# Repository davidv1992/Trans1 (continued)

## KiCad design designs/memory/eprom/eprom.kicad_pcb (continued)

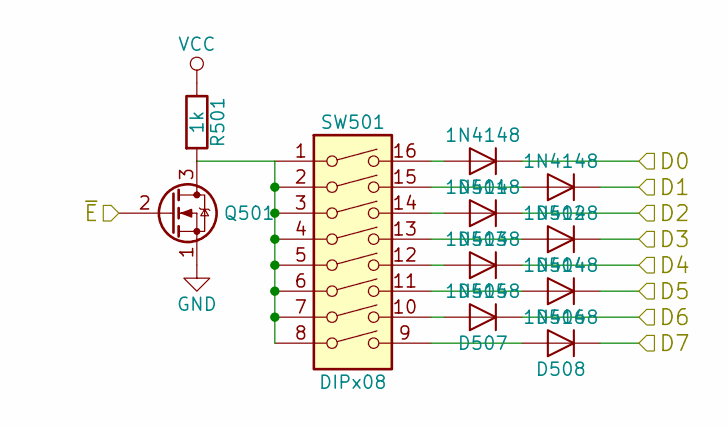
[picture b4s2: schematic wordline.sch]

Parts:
D201, D202, D203, D204, D205, D206, D207, D208: 1N4148; D_default
Q201: 2N7000; TO-92-FET
R201: 1k; R_small
SW201: DIPx08; DIPx8

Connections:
/wordline_0/D0: D201.1 (K); also elsewhere on the board
/wordline_0/D1: D202.1 (K); also elsewhere on the board
/wordline_0/D2: D203.1 (K); also elsewhere on the board
/wordline_0/D3: D204.1 (K); also elsewhere on the board
/wordline_0/~E: Q201.2 (G); also elsewhere on the board
/wordline_4/D0: D208.1 (K); also elsewhere on the board
/wordline_4/D1: D207.1 (K); also elsewhere on the board
/wordline_4/D2: D206.1 (K); also elsewhere on the board
/wordline_4/D3: D205.1 (K); also elsewhere on the board
GND: Q201.1 (S); also elsewhere on the board
unnamed: D201.2 (A), SW201.16
unnamed: D202.2 (A), SW201.15
unnamed: D203.2 (A), SW201.14
unnamed: D204.2 (A), SW201.13
unnamed: D205.2 (A), SW201.12
unnamed: D206.2 (A), SW201.11
unnamed: D207.2 (A), SW201.10
unnamed: D208.2 (A), SW201.9
unnamed: Q201.3 (D), R201.2, SW201.1, SW201.2, SW201.3, SW201.4, SW201.5, SW201.6, SW201.7, SW201.8
VCC: R201.1; also elsewhere on the board

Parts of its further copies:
D301, D302, D303, D304, D305, D306, D307, D308, D401, D402, D403, D404, D405, D406, D407, D408, D501, D502, D503, D504, D505, D506, D507, D508, D601, D602, D603, D604, D605, D606, D607, D608, D701, D702, D703, D704, D705, D706, D707, D708, D801, D802, D803, D804, D805, D806, D807, D808, D901, D902, D903, D904, D905, D906, D907, D908: 1N4148; D_default
Q301, Q401, Q501, Q601, Q701, Q801, Q901: 2N7000; TO-92-FET
R301, R401, R501, R601, R701, R801, R901: 1k; R_small
SW301, SW401, SW501, SW601, SW701, SW801, SW901: DIPx08; DIPx8

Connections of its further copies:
/wordline_0/D0: D301.1 (K), D401.1 (K), D501.1 (K), D608.1 (K), D708.1 (K), D808.1 (K), D908.1 (K); also elsewhere on the board
/wordline_0/D1: D302.1 (K), D402.1 (K), D502.1 (K), D607.1 (K), D707.1 (K), D807.1 (K), D907.1 (K); also elsewhere on the board
/wordline_0/D2: D303.1 (K), D403.1 (K), D503.1 (K), D606.1 (K), D706.1 (K), D806.1 (K), D906.1 (K); also elsewhere on the board
/wordline_0/D3: D304.1 (K), D404.1 (K), D504.1 (K), D605.1 (K), D705.1 (K), D805.1 (K), D905.1 (K); also elsewhere on the board
/wordline_1/~E: Q301.2 (G); also elsewhere on the board
/wordline_2/~E: Q401.2 (G); also elsewhere on the board
/wordline_3/~E: Q501.2 (G); also elsewhere on the board
/wordline_4/D0: D308.1 (K), D408.1 (K), D508.1 (K), D601.1 (K), D701.1 (K), D801.1 (K), D901.1 (K); also elsewhere on the board
/wordline_4/D1: D307.1 (K), D407.1 (K), D507.1 (K), D602.1 (K), D702.1 (K), D802.1 (K), D902.1 (K); also elsewhere on the board
/wordline_4/D2: D306.1 (K), D406.1 (K), D506.1 (K), D603.1 (K), D703.1 (K), D803.1 (K), D903.1 (K); also elsewhere on the board
/wordline_4/D3: D305.1 (K), D405.1 (K), D505.1 (K), D604.1 (K), D704.1 (K), D804.1 (K), D904.1 (K); also elsewhere on the board
/wordline_4/~E: Q601.2 (G); also elsewhere on the board
/wordline_5/~E: Q701.2 (G); also elsewhere on the board
/wordline_6/~E: Q801.2 (G); also elsewhere on the board
/wordline_7/~E: Q901.2 (G); also elsewhere on the board
GND: Q301.1 (S), Q401.1 (S), Q501.1 (S), Q601.1 (S), Q701.1 (S), Q801.1 (S), Q901.1 (S); also elsewhere on the board
unnamed: D301.2 (A), SW301.16
unnamed: D302.2 (A), SW301.15
unnamed: D303.2 (A), SW301.14
unnamed: D304.2 (A), SW301.13
unnamed: D305.2 (A), SW301.12
unnamed: D306.2 (A), SW301.11
unnamed: D307.2 (A), SW301.10
unnamed: D308.2 (A), SW301.9
unnamed: D401.2 (A), SW401.16
unnamed: D402.2 (A), SW401.15
unnamed: D403.2 (A), SW401.14
unnamed: D404.2 (A), SW401.13
unnamed: D405.2 (A), SW401.12
unnamed: D406.2 (A), SW401.11
unnamed: D407.2 (A), SW401.10
unnamed: D408.2 (A), SW401.9
unnamed: D501.2 (A), SW501.16
unnamed: D502.2 (A), SW501.15
unnamed: D503.2 (A), SW501.14
unnamed: D504.2 (A), SW501.13
unnamed: D505.2 (A), SW501.12
unnamed: D506.2 (A), SW501.11
unnamed: D507.2 (A), SW501.10
unnamed: D508.2 (A), SW501.9
unnamed: D601.2 (A), SW601.16
unnamed: D602.2 (A), SW601.15
unnamed: D603.2 (A), SW601.14
unnamed: D604.2 (A), SW601.13
unnamed: D605.2 (A), SW601.12
unnamed: D606.2 (A), SW601.11
unnamed: D607.2 (A), SW601.10
unnamed: D608.2 (A), SW601.9
unnamed: D701.2 (A), SW701.16
unnamed: D702.2 (A), SW701.15
unnamed: D703.2 (A), SW701.14
unnamed: D704.2 (A), SW701.13
unnamed: D705.2 (A), SW701.12
unnamed: D706.2 (A), SW701.11
unnamed: D707.2 (A), SW701.10
unnamed: D708.2 (A), SW701.9
unnamed: D801.2 (A), SW801.16
unnamed: D802.2 (A), SW801.15
unnamed: D803.2 (A), SW801.14
unnamed: D804.2 (A), SW801.13
unnamed: D805.2 (A), SW801.12
unnamed: D806.2 (A), SW801.11
unnamed: D807.2 (A), SW801.10
unnamed: D808.2 (A), SW801.9
unnamed: D901.2 (A), SW901.16
unnamed: D902.2 (A), SW901.15
unnamed: D903.2 (A), SW901.14
unnamed: D904.2 (A), SW901.13
unnamed: D905.2 (A), SW901.12
unnamed: D906.2 (A), SW901.11
unnamed: D907.2 (A), SW901.10
unnamed: D908.2 (A), SW901.9
unnamed: Q301.3 (D), R301.2, SW301.1, SW301.2, SW301.3, SW301.4, SW301.5, SW301.6, SW301.7, SW301.8
unnamed: Q401.3 (D), R401.2, SW401.1, SW401.2, SW401.3, SW401.4, SW401.5, SW401.6, SW401.7, SW401.8
unnamed: Q501.3 (D), R501.2, SW501.1, SW501.2, SW501.3, SW501.4, SW501.5, SW501.6, SW501.7, SW501.8
unnamed: Q601.3 (D), R601.2, SW601.1, SW601.2, SW601.3, SW601.4, SW601.5, SW601.6, SW601.7, SW601.8
unnamed: Q701.3 (D), R701.2, SW701.1, SW701.2, SW701.3, SW701.4, SW701.5, SW701.6, SW701.7, SW701.8
unnamed: Q801.3 (D), R801.2, SW801.1, SW801.2, SW801.3, SW801.4, SW801.5, SW801.6, SW801.7, SW801.8
unnamed: Q901.3 (D), R901.2, SW901.1, SW901.2, SW901.3, SW901.4, SW901.5, SW901.6, SW901.7, SW901.8
VCC: R301.1, R401.1, R501.1, R601.1, R701.1, R801.1, R901.1; also elsewhere on the board

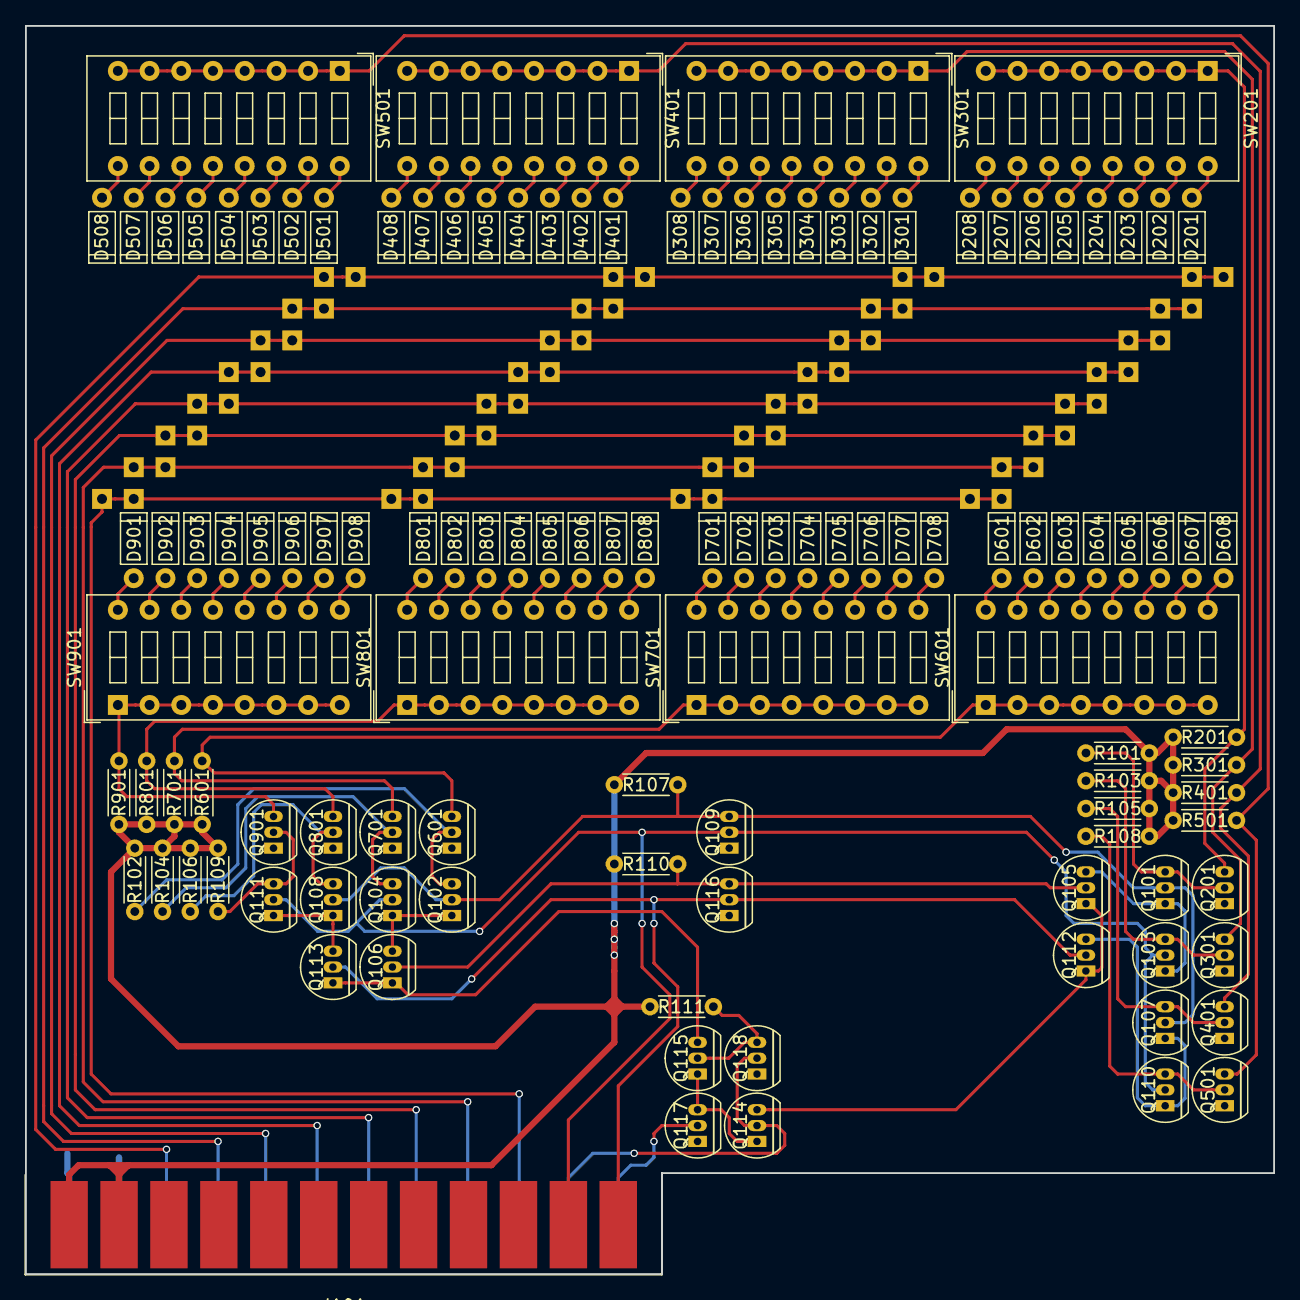
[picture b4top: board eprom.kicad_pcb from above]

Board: 2 copper layers, 100.0 x 100.0 mm, 118 parts (0 on the bottom side), 104 nets.

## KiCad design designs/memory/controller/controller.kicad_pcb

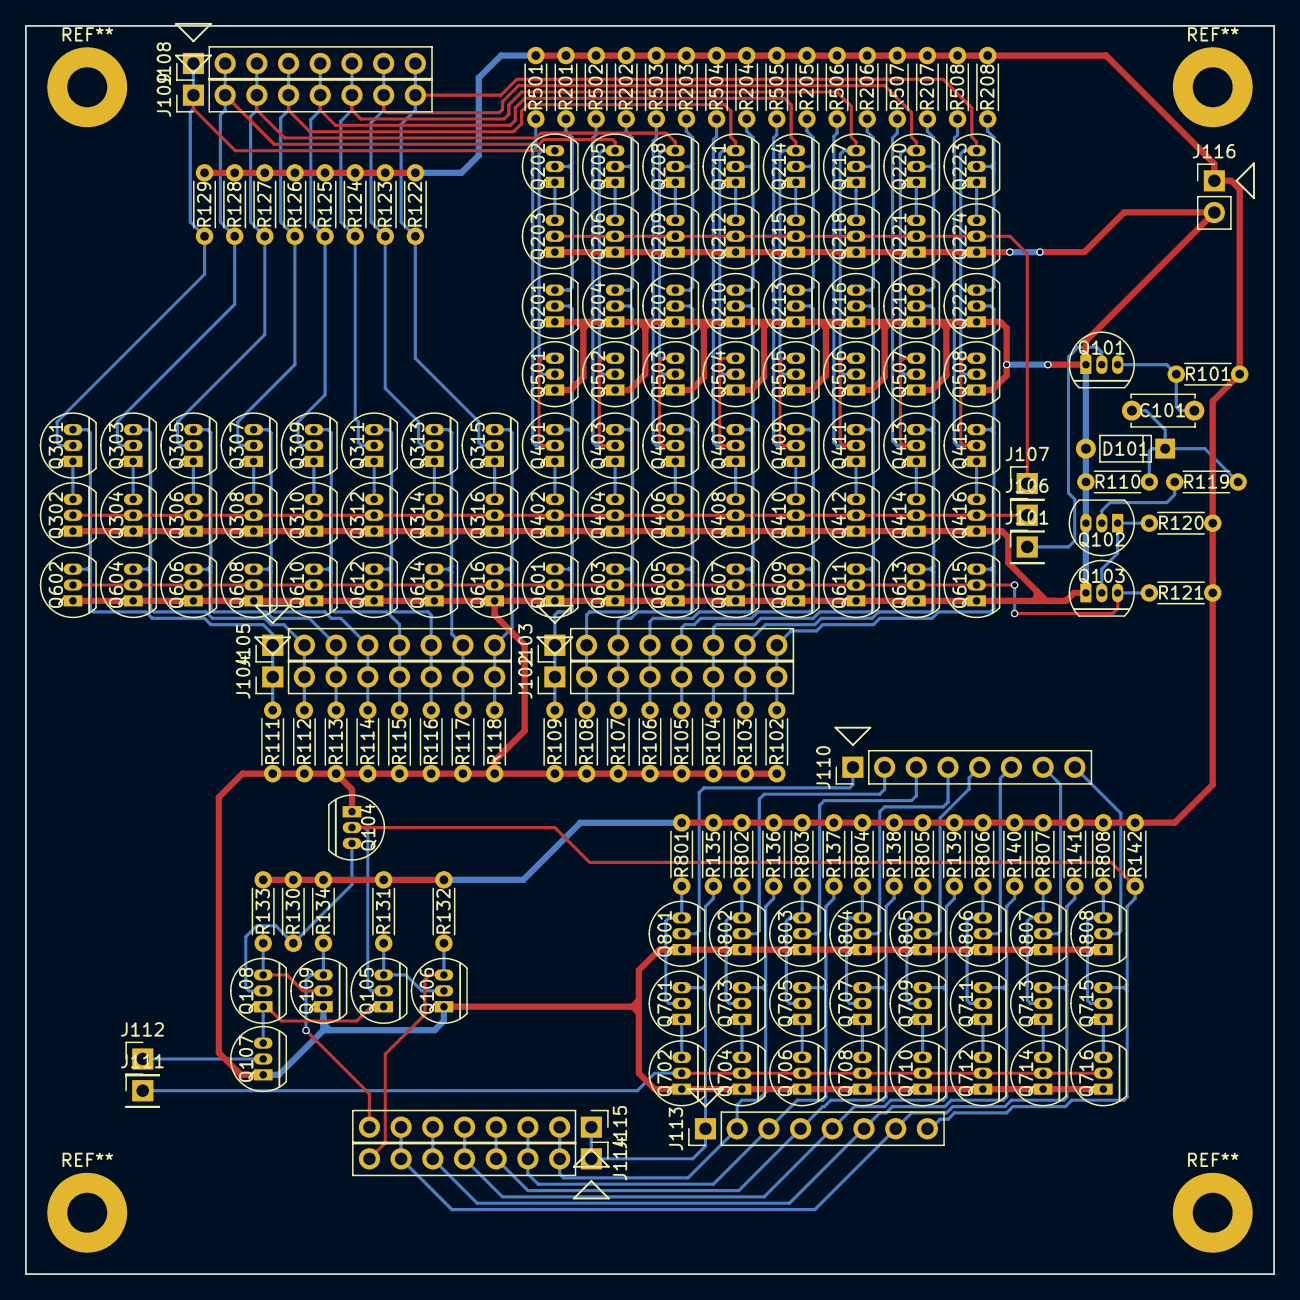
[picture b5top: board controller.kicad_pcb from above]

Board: 2 copper layers, 100.0 x 100.0 mm, 197 parts (0 on the bottom side), 114 nets.

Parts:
C101: 100pf; C_default
D101: 1N4148; D_default
J101, J106, J107, J111, J112: Conn_01x01; PH_1x1
J102, J103, J104, J105, J108, J109, J110, J113, J114, J115: Conn_01x08; PH_1x8
J116: Conn_01x02_Power; PH_1x2
Q101, Q103, Q104, Q105, Q106, Q107, Q108, Q109, Q201, Q202, Q203, Q204, Q205, Q206, Q207, Q208, Q209, Q210, Q211, Q212, Q213, Q214, Q215, Q216, Q217, Q218, Q219, Q220, Q221, Q222, Q223, Q224, Q301, Q302, Q303, Q304, Q305, Q306, Q307, Q308, Q309, Q310, Q311, Q312, Q313, Q314, Q315, Q316, Q401, Q402, Q403, Q404, Q405, Q406, Q407, Q408, Q409, Q410, Q411, Q412, Q413, Q414, Q415, Q416, Q501, Q502, Q503, Q504, Q505, Q506, Q507, Q508, Q601, Q602, Q603, Q604, Q605, Q606, Q607, Q608, Q609, Q610, Q611, Q612, Q613, Q614, Q615, Q616, Q701, Q702, Q703, Q704, Q705, Q706, Q707, Q708, Q709, Q710, Q711, Q712, Q713, Q714, Q715, Q716, Q801, Q802, Q803, Q804, Q805, Q806, Q807, Q808: 2N7000; TO-92-FET
Q102: BC547; TO-92-BJT
R101, R110, R120, R121, R122, R123, R124, R125, R126, R127, R128, R129, R130, R131, R132, R133, R134, R135, R136, R137, R138, R139, R140, R141, R142, R501, R502, R503, R504, R505, R506, R507, R508, R801, R802, R803, R804, R805, R806, R807, R808: 1k; R_small
R102, R103, R104, R105, R106, R107, R108, R109, R111, R112, R113, R114, R115, R116, R117, R118: 100k; R_small
R119: 10k; R_small
R201, R202, R203, R204, R205, R206, R207, R208: R; R_small

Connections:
/Ten/A0: J113.1, J114.1, J115.1, Q701.3, R135.2
/Ten/A1: J113.2, J114.2, J115.2, Q703.3, R136.2
/Ten/A2: J113.3, J114.3, J115.3, Q705.3, R137.2
/Ten/A3: J113.4, J114.4, J115.4, Q707.3, R138.2
/Ten/A4: J113.5, J114.5, J115.5, Q709.3, R139.2
/Ten/A5: J113.6, J114.6, J115.6, Q711.3, R140.2
/Ten/A6: J113.7, J114.7, J115.7, Q713.3, R141.2
/Ten/A7: J113.8, Q104.2, Q105.2, Q715.3, R142.2
/Ten/En: J111.1, Q702.2, Q704.2, Q706.2, Q708.2, Q710.2, Q712.2, Q714.2, Q716.2
/Ten/T0: Q701.2, Q801.3, R801.2
/Ten/T1: Q703.2, Q802.3, R802.2
/Ten/T2: Q705.2, Q803.3, R803.2
/Ten/T3: Q707.2, Q804.3, R804.2
/Ten/T4: Q709.2, Q805.3, R805.2
/Ten/T5: Q711.2, Q806.3, R806.2
/Ten/T6: Q713.2, Q807.3, R807.2
/Ten/T7: Q715.2, Q808.3, R808.2
/clear/Clr: Q103.3, Q601.2, Q602.2, Q603.2, Q604.2, Q605.2, Q606.2, Q607.2, Q608.2, Q609.2, Q610.2, Q611.2, Q612.2, Q613.2, Q614.2, Q615.2, Q616.2, R121.2
/clear/D0: J102.1, J103.1, Q201.2, Q401.3, Q601.3, R109.2
/clear/D1: J102.2, J103.2, Q204.2, Q403.3, Q603.3, R108.2
/clear/D2: J102.3, J103.3, Q207.2, Q405.3, Q605.3, R107.2
/clear/D3: J102.4, J103.4, Q210.2, Q407.3, Q607.3, R106.2
/clear/D4: J102.5, J103.5, Q213.2, Q409.3, Q609.3, R105.2
/clear/D5: J102.6, J103.6, Q216.2, Q411.3, Q611.3, R104.2
/clear/D6: J102.7, J103.7, Q219.2, Q413.3, Q613.3, R103.2
/clear/D7: J102.8, J103.8, Q222.2, Q415.3, Q615.3, R102.2
/clear/D8: J104.1, J105.1, Q301.3, Q602.3, R111.1
/clear/D9: J104.2, J105.2, Q303.3, Q604.3, R112.1
/clear/D10: J104.3, J105.3, Q305.3, Q606.3, R113.1
/clear/D11: J104.4, J105.4, Q307.3, Q608.3, R114.1
/clear/D12: J104.5, J105.5, Q309.3, Q610.3, R115.1
/clear/D13: J104.6, J105.6, Q311.3, Q612.3, R116.1
/clear/D14: J104.7, J105.7, Q313.3, Q614.3, R117.1
/clear/D15: J104.8, J105.8, Q315.3, Q616.3, R118.1
/inv2/D0: J110.1, Q801.2
/inv2/D1: J110.2, Q802.2
/inv2/D2: J110.3, Q803.2
/inv2/D3: J110.4, Q804.2
/inv2/D4: J110.5, Q805.2
/inv2/D5: J110.6, Q806.2
/inv2/D6: J110.7, Q807.2
/inv2/D7: J110.8, Q808.2
/inv/D0: J108.1, J109.1, Q202.3, Q301.2, Q501.2, R129.2
/inv/D1: J108.2, J109.2, Q205.3, Q303.2, Q502.2, R128.2
/inv/D2: J108.3, J109.3, Q208.3, Q305.2, Q503.2, R127.2
/inv/D3: J108.4, J109.4, Q211.3, Q307.2, Q504.2, R126.2
/inv/D4: J108.5, J109.5, Q214.3, Q309.2, Q505.2, R125.2
/inv/D5: J108.6, J109.6, Q217.3, Q311.2, Q506.2, R124.2
/inv/D6: J108.7, J109.7, Q220.3, Q313.2, Q507.2, R123.2
/inv/D7: J108.8, J109.8, Q223.3, Q315.2, Q508.2, R122.2
/sense/En: J107.1, Q203.2, Q206.2, Q209.2, Q212.2, Q215.2, Q218.2, Q221.2, Q224.2
/writeNeg/En: J106.1, Q302.2, Q304.2, Q306.2, Q308.2, Q310.2, Q312.2, Q314.2, Q316.2, Q402.2, Q404.2, Q406.2, Q408.2, Q410.2, Q412.2, Q414.2, Q416.2
/writePos/D0: Q401.2, Q501.3, R501.2
/writePos/D1: Q403.2, Q502.3, R502.2
/writePos/D2: Q405.2, Q503.3, R503.2
/writePos/D3: Q407.2, Q504.3, R504.2
/writePos/D4: Q409.2, Q505.3, R505.2
/writePos/D5: Q411.2, Q506.3, R506.2
/writePos/D6: Q413.2, Q507.3, R507.2
/writePos/D7: Q415.2, Q508.3, R508.2
GND: D101.2, J116.2, Q101.1, Q102.3, Q103.1, Q104.1, Q106.1, Q107.1, Q109.1, Q201.1, Q203.1, Q204.1, Q206.1, Q207.1, Q209.1, Q210.1, Q212.1, Q213.1, Q215.1, Q216.1, Q218.1, Q219.1, Q221.1, Q222.1, Q224.1, Q302.1, Q304.1, Q306.1, Q308.1, Q310.1, Q312.1, Q314.1, Q316.1, Q402.1, Q404.1, Q406.1, Q408.1, Q410.1, Q412.1, Q414.1, Q416.1, Q501.1, Q502.1, Q503.1, Q504.1, Q505.1, Q506.1, Q507.1, Q508.1, Q601.1, Q602.1, Q603.1, Q604.1, Q605.1, Q606.1, Q607.1, Q608.1, Q609.1, Q610.1, Q611.1, Q612.1, Q613.1, Q614.1, Q615.1, Q616.1, Q702.1, Q704.1, Q706.1, Q708.1, Q710.1, Q712.1, Q714.1, Q716.1, Q801.1, Q802.1, Q803.1, Q804.1, Q805.1, Q806.1, Q807.1, Q808.1, R102.1, R103.1, R104.1, R105.1, R106.1, R107.1, R108.1, R109.1, R110.2, R111.2, R112.2, R113.2, R114.2, R115.2, R116.2, R117.2, R118.2
unnamed: C101.1, Q101.3, R101.2
unnamed: C101.2, D101.1, R110.1, R119.2
unnamed: J101.1, Q101.2
unnamed: J112.1, Q107.2
unnamed: J114.8, Q106.3, R132.2
unnamed: J115.8, Q109.3, R134.2
unnamed: Q102.1, Q103.2, R120.2
unnamed: Q102.2, R119.1
unnamed: Q104.3, Q108.2, R130.2
unnamed: Q105.1, Q107.3, Q108.1
unnamed: Q105.3, Q106.2, R131.2
unnamed: Q108.3, Q109.2, R133.2
unnamed: Q201.3, Q202.2, R201.2
unnamed: Q202.1, Q203.3
unnamed: Q204.3, Q205.2, R202.2
unnamed: Q205.1, Q206.3
unnamed: Q207.3, Q208.2, R203.2
unnamed: Q208.1, Q209.3
unnamed: Q210.3, Q211.2, R204.2
unnamed: Q211.1, Q212.3
unnamed: Q213.3, Q214.2, R205.2
unnamed: Q214.1, Q215.3
unnamed: Q216.3, Q217.2, R206.2
unnamed: Q217.1, Q218.3
unnamed: Q219.3, Q220.2, R207.2
unnamed: Q220.1, Q221.3
unnamed: Q222.3, Q223.2, R208.2
unnamed: Q223.1, Q224.3
unnamed: Q301.1, Q302.3
unnamed: Q303.1, Q304.3
unnamed: Q305.1, Q306.3
unnamed: Q307.1, Q308.3
unnamed: Q309.1, Q310.3
unnamed: Q311.1, Q312.3
unnamed: Q313.1, Q314.3
unnamed: Q315.1, Q316.3
unnamed: Q401.1, Q402.3
unnamed: Q403.1, Q404.3
unnamed: Q405.1, Q406.3
unnamed: Q407.1, Q408.3
unnamed: Q409.1, Q410.3
unnamed: Q411.1, Q412.3
unnamed: Q413.1, Q414.3
unnamed: Q415.1, Q416.3
unnamed: Q701.1, Q702.3
unnamed: Q703.1, Q704.3
unnamed: Q705.1, Q706.3
unnamed: Q707.1, Q708.3
unnamed: Q709.1, Q710.3
unnamed: Q711.1, Q712.3
unnamed: Q713.1, Q714.3
unnamed: Q715.1, Q716.3
VCC: J116.1, R101.1, R120.1, R121.1, R122.1, R123.1, R124.1, R125.1, R126.1, R127.1, R128.1, R129.1, R130.1, R131.1, R132.1, R133.1, R134.1, R135.1, R136.1, R137.1, R138.1, R139.1, R140.1, R141.1, R142.1, R201.1, R202.1, R203.1, R204.1, R205.1, R206.1, R207.1, R208.1, R501.1, R502.1, R503.1, R504.1, R505.1, R506.1, R507.1, R508.1, R801.1, R802.1, R803.1, R804.1, R805.1, R806.1, R807.1, R808.1

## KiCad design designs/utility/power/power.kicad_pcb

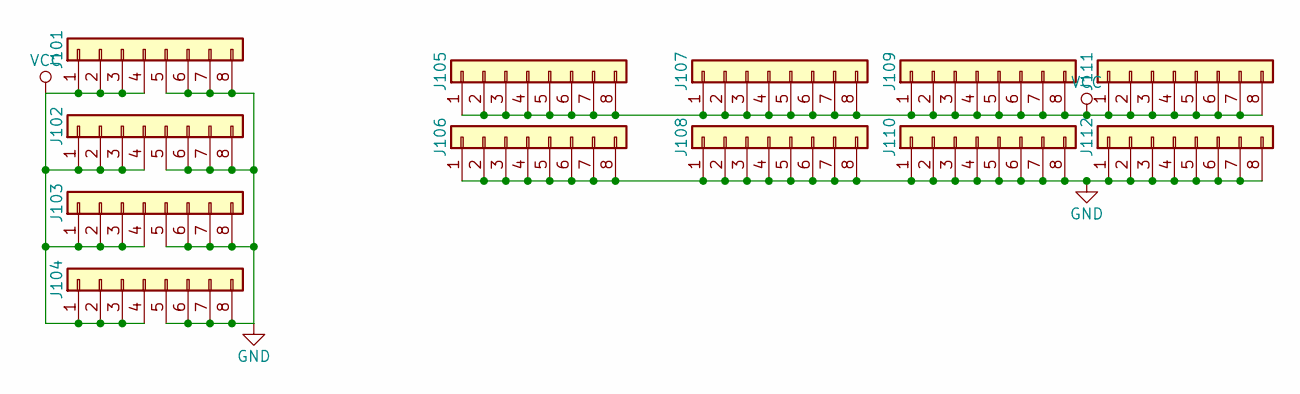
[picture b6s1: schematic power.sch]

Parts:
J101, J102, J103, J104, J105, J106, J107, J108, J109, J110, J111, J112: Conn_01x08; PH_1x8

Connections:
GND: J101.5, J101.6, J101.7, J101.8, J102.5, J102.6, J102.7, J102.8, J103.5, J103.6, J103.7, J103.8, J104.5, J104.6, J104.7, J104.8, J106.1, J106.2, J106.3, J106.4, J106.5, J106.6, J106.7, J106.8, J108.1, J108.2, J108.3, J108.4, J108.5, J108.6, J108.7, J108.8, J110.1, J110.2, J110.3, J110.4, J110.5, J110.6, J110.7, J110.8, J112.1, J112.2, J112.3, J112.4, J112.5, J112.6, J112.7, J112.8
VCC: J101.1, J101.2, J101.3, J101.4, J102.1, J102.2, J102.3, J102.4, J103.1, J103.2, J103.3, J103.4, J104.1, J104.2, J104.3, J104.4, J105.1, J105.2, J105.3, J105.4, J105.5, J105.6, J105.7, J105.8, J107.1, J107.2, J107.3, J107.4, J107.5, J107.6, J107.7, J107.8, J109.1, J109.2, J109.3, J109.4, J109.5, J109.6, J109.7, J109.8, J111.1, J111.2, J111.3, J111.4, J111.5, J111.6, J111.7, J111.8

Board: 2 copper layers, 12 parts (0 on the bottom side), 2 nets, no tracks yet.

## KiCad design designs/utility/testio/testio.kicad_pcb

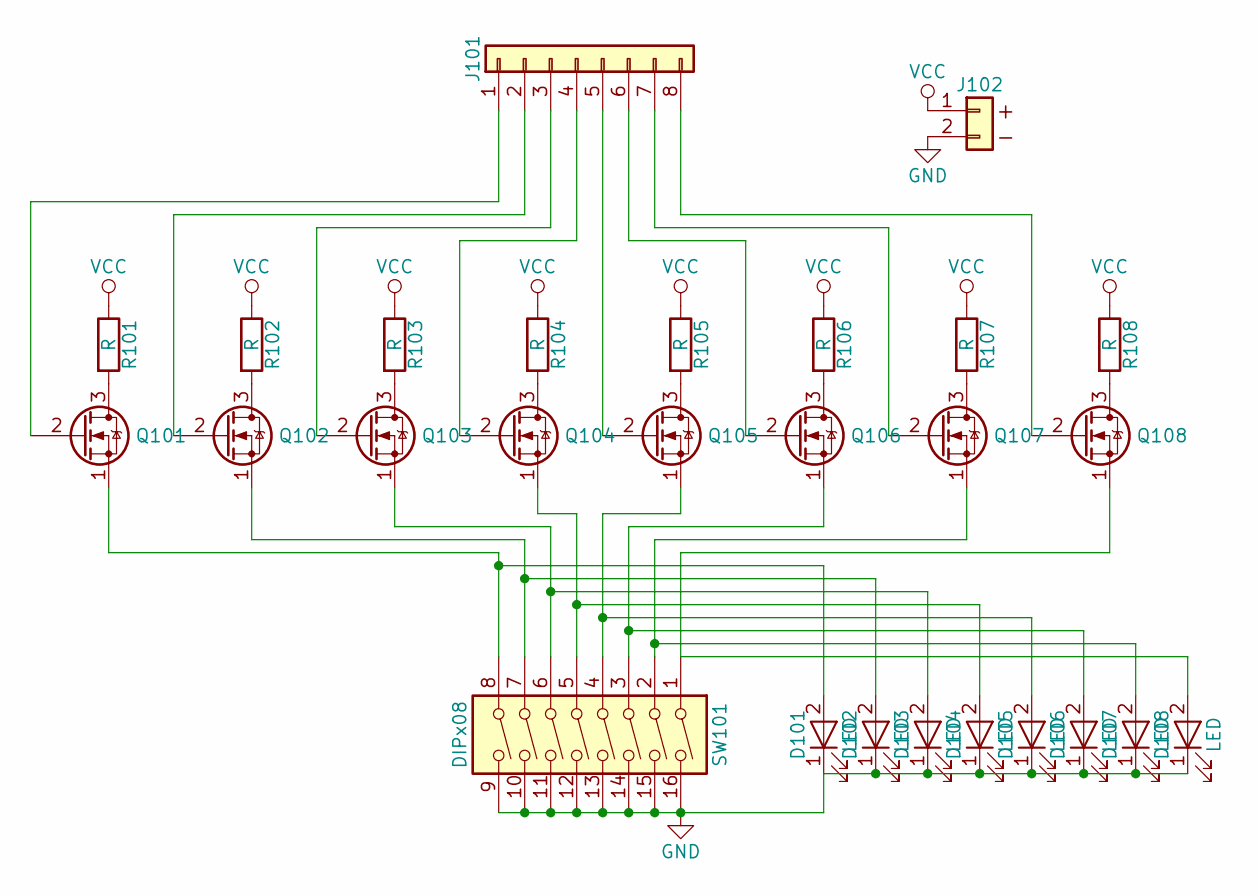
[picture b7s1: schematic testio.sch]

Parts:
D101, D102, D103, D104, D105, D106, D107, D108: LED; LED_D3.0mm
J101: Conn_01x08; PH_1x8
J102: Conn_01x02_Power; PH_1x2
Q101, Q102, Q103, Q104, Q105, Q106, Q107, Q108: 2N7000; TO-92-FET
R101, R102, R103, R104, R105, R106, R107, R108: R; R_small
SW101: DIPx08; DIPx8

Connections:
GND: D101.1 (K), D102.1 (K), D103.1 (K), D104.1 (K), D105.1 (K), D106.1 (K), D107.1 (K), D108.1 (K), J102.2, SW101.9, SW101.10, SW101.11, SW101.12, SW101.13, SW101.14, SW101.15, SW101.16
unnamed: D101.2 (A), Q101.1 (S), SW101.8
unnamed: D102.2 (A), Q102.1 (S), SW101.7
unnamed: D103.2 (A), Q103.1 (S), SW101.6
unnamed: D104.2 (A), Q104.1 (S), SW101.5
unnamed: D105.2 (A), Q105.1 (S), SW101.4
unnamed: D106.2 (A), Q106.1 (S), SW101.3
unnamed: D107.2 (A), Q107.1 (S), SW101.2
unnamed: D108.2 (A), Q108.1 (S), SW101.1
unnamed: J101.1, Q101.2 (G)
unnamed: J101.2, Q102.2 (G)
unnamed: J101.3, Q103.2 (G)
unnamed: J101.4, Q104.2 (G)
unnamed: J101.5, Q105.2 (G)
unnamed: J101.6, Q106.2 (G)
unnamed: J101.7, Q107.2 (G)
unnamed: J101.8, Q108.2 (G)
unnamed: Q101.3 (D), R101.2
unnamed: Q102.3 (D), R102.2
unnamed: Q103.3 (D), R103.2
unnamed: Q104.3 (D), R104.2
unnamed: Q105.3 (D), R105.2
unnamed: Q106.3 (D), R106.2
unnamed: Q107.3 (D), R107.2
unnamed: Q108.3 (D), R108.2
VCC: J102.1, R101.1, R102.1, R103.1, R104.1, R105.1, R106.1, R107.1, R108.1

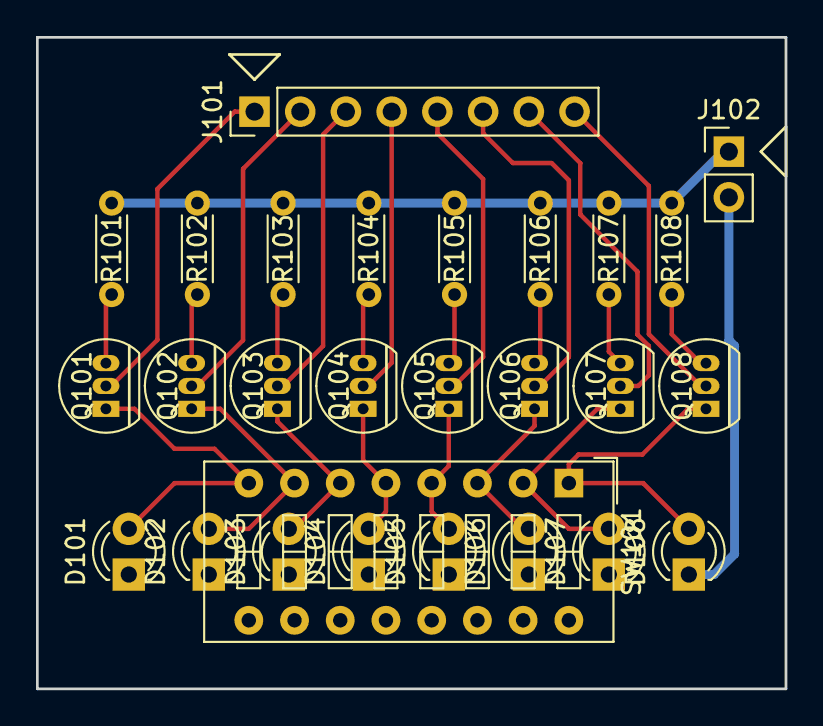
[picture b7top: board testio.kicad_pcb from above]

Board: 2 copper layers, 41.6 x 36.2 mm, 27 parts (0 on the bottom side), 26 nets.

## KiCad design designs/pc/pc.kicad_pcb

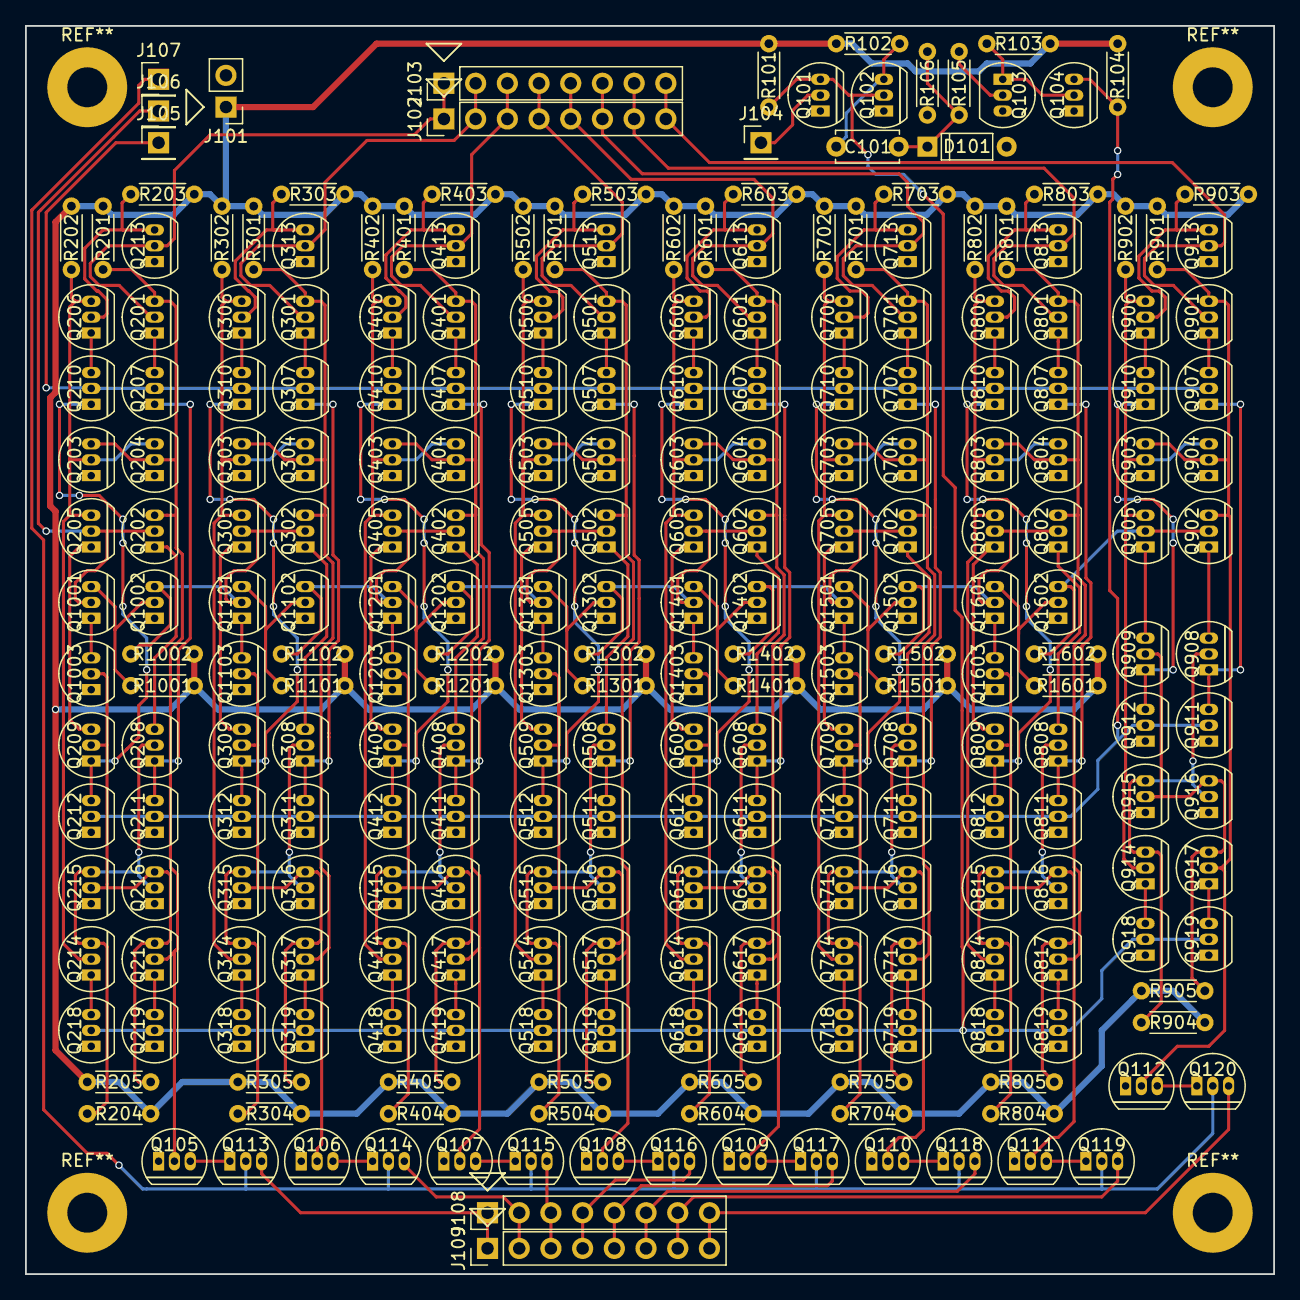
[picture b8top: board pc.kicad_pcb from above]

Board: 2 copper layers, 100.0 x 100.0 mm, 264 parts (0 on the bottom side), 161 nets.

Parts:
C101: 100pF; C_default
D101: 1N4148; D_default
J101: Conn_01x02_Power; PH_1x2
J102, J103, J108, J109: Conn_01x08; PH_1x8
J104, J105, J106, J107: Conn_01x01; PH_1x1
Q101, Q102, Q104, Q105, Q106, Q107, Q108, Q109, Q110, Q111, Q112, Q113, Q114, Q115, Q116, Q117, Q118, Q119, Q120, Q201, Q202, Q203, Q204, Q205, Q206, Q207, Q208, Q209, Q210, Q211, Q212, Q213, Q214, Q215, Q216, Q217, Q218, Q219, Q301, Q302, Q303, Q304, Q305, Q306, Q307, Q308, Q309, Q310, Q311, Q312, Q313, Q314, Q315, Q316, Q317, Q318, Q319, Q401, Q402, Q403, Q404, Q405, Q406, Q407, Q408, Q409, Q410, Q411, Q412, Q413, Q414, Q415, Q416, Q417, Q418, Q419, Q501, Q502, Q503, Q504, Q505, Q506, Q507, Q508, Q509, Q510, Q511, Q512, Q513, Q514, Q515, Q516, Q517, Q518, Q519, Q601, Q602, Q603, Q604, Q605, Q606, Q607, Q608, Q609, Q610, Q611, Q612, Q613, Q614, Q615, Q616, Q617, Q618, Q619, Q701, Q702, Q703, Q704, Q705, Q706, Q707, Q708, Q709, Q710, Q711, Q712, Q713, Q714, Q715, Q716, Q717, Q718, Q719, Q801, Q802, Q803, Q804, Q805, Q806, Q807, Q808, Q809, Q810, Q811, Q812, Q813, Q814, Q815, Q816, Q817, Q818, Q819, Q901, Q902, Q903, Q904, Q905, Q906, Q907, Q908, Q909, Q910, Q911, Q912, Q913, Q914, Q915, Q916, Q917, Q918, Q919, Q1001, Q1002, Q1003, Q1101, Q1102, Q1103, Q1201, Q1202, Q1203, Q1301, Q1302, Q1303, Q1401, Q1402, Q1403, Q1501, Q1502, Q1503, Q1601, Q1602, Q1603: 2N7000; TO-92-FET
Q103: BC547; TO-92-BJT
R101, R102, R103, R104, R201, R202, R203, R204, R205, R301, R302, R303, R304, R305, R401, R402, R403, R404, R405, R501, R502, R503, R504, R505, R601, R602, R603, R604, R605, R701, R702, R703, R704, R705, R801, R802, R803, R804, R805, R901, R902, R903, R904, R905, R1001, R1002, R1101, R1102, R1201, R1202, R1301, R1302, R1401, R1402, R1501, R1502, R1601, R1602: 1k; R_small
R105, R106: 10k; R_small

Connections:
/pcbit0/C: Q104.3, Q211.2, Q212.2, Q311.2, Q312.2, Q411.2, Q412.2, Q511.2, Q512.2, Q611.2, Q612.2, Q711.2, Q712.2, Q811.2, Q812.2, Q911.2, Q912.2, R104.2
/pcbit0/Ca: Q209.2, Q215.2, Q216.3, Q217.3, Q1003.2, R205.2
/pcbit0/D: J102.1, J103.1, Q201.2, Q213.2
/pcbit0/DEn: J105.1, Q207.2, Q210.2, Q307.2, Q310.2, Q407.2, Q410.2, Q507.2, Q510.2, Q607.2, Q610.2, Q707.2, Q710.2, Q807.2, Q810.2, Q907.2, Q910.2
/pcbit0/Q: Q203.2, Q204.3, Q205.3, Q206.3, Q214.2, R202.2
/pcbit0/~C~: Q101.3, Q102.2, Q218.2, Q219.2, Q318.2, Q319.2, Q418.2, Q419.2, Q518.2, Q519.2, Q618.2, Q619.2, Q718.2, Q719.2, Q818.2, Q819.2, Q918.2, Q919.2, R101.2
/pcbit0/~Q~: Q105.2, Q201.3, Q202.3, Q203.3, Q204.2, Q217.2, R201.2
/pcbit1/Ca: Q309.2, Q315.2, Q316.3, Q317.3, Q1103.2, R305.2
/pcbit1/D: J102.2, J103.2, Q301.2, Q313.2
/pcbit1/Q: Q303.2, Q304.3, Q305.3, Q306.3, Q314.2, R302.2
/pcbit1/~Q~: Q106.2, Q301.3, Q302.3, Q303.3, Q304.2, Q317.2, R301.2
/pcbit2/Ca: Q409.2, Q415.2, Q416.3, Q417.3, Q1203.2, R405.2
/pcbit2/D: J102.3, J103.3, Q401.2, Q413.2
/pcbit2/Q: Q403.2, Q404.3, Q405.3, Q406.3, Q414.2, R402.2
/pcbit2/~Q~: Q107.2, Q401.3, Q402.3, Q403.3, Q404.2, Q417.2, R401.2
/pcbit3/Ca: Q509.2, Q515.2, Q516.3, Q517.3, Q1303.2, R505.2
/pcbit3/D: J102.4, J103.4, Q501.2, Q513.2
/pcbit3/Q: Q503.2, Q504.3, Q505.3, Q506.3, Q514.2, R502.2
/pcbit3/~Q~: Q108.2, Q501.3, Q502.3, Q503.3, Q504.2, Q517.2, R501.2
/pcbit4/Ca: Q609.2, Q615.2, Q616.3, Q617.3, Q1403.2, R605.2
/pcbit4/D: J102.5, J103.5, Q601.2, Q613.2
/pcbit4/Q: Q603.2, Q604.3, Q605.3, Q606.3, Q614.2, R602.2
/pcbit4/~Q~: Q109.2, Q601.3, Q602.3, Q603.3, Q604.2, Q617.2, R601.2
/pcbit5/Ca: Q709.2, Q715.2, Q716.3, Q717.3, Q1503.2, R705.2
/pcbit5/D: J102.6, J103.6, Q701.2, Q713.2
/pcbit5/Q: Q703.2, Q704.3, Q705.3, Q706.3, Q714.2, R702.2
/pcbit5/~Q~: Q110.2, Q701.3, Q702.3, Q703.3, Q704.2, Q717.2, R701.2
/pcbit6/Ca: Q809.2, Q815.2, Q816.3, Q817.3, Q1603.2, R805.2
/pcbit6/D: J102.7, J103.7, Q801.2, Q813.2
/pcbit6/Q: Q803.2, Q804.3, Q805.3, Q806.3, Q814.2, R802.2
/pcbit6/~Q~: Q111.2, Q801.3, Q802.3, Q803.3, Q804.2, Q817.2, R801.2
/pcbit7/Ca: Q909.2, Q915.2, Q916.3, Q917.3, R905.2
/pcbit7/D: J102.8, J103.8, Q901.2, Q913.2
/pcbit7/Q: Q903.2, Q904.3, Q905.3, Q906.3, Q914.2, R902.2
/pcbit7/~Q~: Q112.2, Q901.3, Q902.3, Q903.3, Q904.2, Q917.2, R901.2
/pcc1/NEn: Q302.2, Q305.2, Q1002.3, Q1101.2, R1002.2
/pcc1/PEn: J106.1, Q202.2, Q205.2, Q1001.2
/sheet5C453C86/NEn: Q702.2, Q705.2, Q1402.3, Q1501.2, R1402.2
/sheet5C453C87/NEn: Q802.2, Q805.2, Q1502.3, Q1601.2, R1502.2
/sheet5C4545D6/NEn: Q902.2, Q905.2, Q1602.3, R1602.2
/sheet5C45280B/NEn: Q402.2, Q405.2, Q1102.3, Q1201.2, R1102.2
/sheet5C453582/NEn: Q502.2, Q505.2, Q1202.3, Q1301.2, R1202.2
/sheet5C453583/NEn: Q602.2, Q605.2, Q1302.3, Q1401.2, R1302.2
GND: D101.2, J101.2, Q101.1, Q102.1, Q103.3, Q104.1, Q105.1, Q106.1, Q107.1, Q108.1, Q109.1, Q110.1, Q111.1, Q112.1, Q203.1, Q204.1, Q211.1, Q212.1, Q213.1, Q215.1, Q216.1, Q218.1, Q219.1, Q303.1, Q304.1, Q311.1, Q312.1, Q313.1, Q315.1, Q316.1, Q318.1, Q319.1, Q403.1, Q404.1, Q411.1, Q412.1, Q413.1, Q415.1, Q416.1, Q418.1, Q419.1, Q503.1, Q504.1, Q511.1, Q512.1, Q513.1, Q515.1, Q516.1, Q518.1, Q519.1, Q603.1, Q604.1, Q611.1, Q612.1, Q613.1, Q615.1, Q616.1, Q618.1, Q619.1, Q703.1, Q704.1, Q711.1, Q712.1, Q713.1, Q715.1, Q716.1, Q718.1, Q719.1, Q803.1, Q804.1, Q811.1, Q812.1, Q813.1, Q815.1, Q816.1, Q818.1, Q819.1, Q903.1, Q904.1, Q911.1, Q912.1, Q913.1, Q915.1, Q916.1, Q918.1, Q919.1, Q1002.1, Q1003.1, Q1102.1, Q1103.1, Q1202.1, Q1203.1, Q1302.1, Q1303.1, Q1402.1, Q1403.1, Q1502.1, Q1503.1, Q1602.1, Q1603.1, R106.2
unnamed: C101.1, Q102.3, R102.2
unnamed: C101.2, D101.1, R105.2, R106.1
unnamed: J104.1, Q101.2
unnamed: J107.1, Q113.2, Q114.2, Q115.2, Q116.2, Q117.2, Q118.2, Q119.2, Q120.2
unnamed: J108.1, J109.1, Q113.3
unnamed: J108.2, J109.2, Q114.3
unnamed: J108.3, J109.3, Q115.3
unnamed: J108.4, J109.4, Q116.3
unnamed: J108.5, J109.5, Q117.3
unnamed: J108.6, J109.6, Q118.3
unnamed: J108.7, J109.7, Q119.3
unnamed: J108.8, J109.8, Q120.3
unnamed: Q103.1, Q104.2, R103.2
unnamed: Q103.2, R105.1
unnamed: Q105.3, Q113.1
unnamed: Q106.3, Q114.1
unnamed: Q107.3, Q115.1
unnamed: Q108.3, Q116.1
unnamed: Q109.3, Q117.1
unnamed: Q110.3, Q118.1
unnamed: Q111.3, Q119.1
unnamed: Q112.3, Q120.1
unnamed: Q201.1, Q207.3
unnamed: Q202.1, Q208.3
unnamed: Q205.1, Q209.3
unnamed: Q206.1, Q210.3
unnamed: Q206.2, Q213.3, R203.2
unnamed: Q207.1, Q208.1, Q211.3
unnamed: Q208.2, Q214.3, Q215.3, Q216.2, R204.2
unnamed: Q209.1, Q210.1, Q212.3
unnamed: Q214.1, Q218.3
unnamed: Q217.1, Q219.3
unnamed: Q301.1, Q307.3
unnamed: Q302.1, Q308.3
unnamed: Q305.1, Q309.3
unnamed: Q306.1, Q310.3
unnamed: Q306.2, Q313.3, R303.2
unnamed: Q307.1, Q308.1, Q311.3
unnamed: Q308.2, Q314.3, Q315.3, Q316.2, R304.2
unnamed: Q309.1, Q310.1, Q312.3
unnamed: Q314.1, Q318.3
unnamed: Q317.1, Q319.3
unnamed: Q401.1, Q407.3
unnamed: Q402.1, Q408.3
unnamed: Q405.1, Q409.3
unnamed: Q406.1, Q410.3
unnamed: Q406.2, Q413.3, R403.2
unnamed: Q407.1, Q408.1, Q411.3
unnamed: Q408.2, Q414.3, Q415.3, Q416.2, R404.2
unnamed: Q409.1, Q410.1, Q412.3
unnamed: Q414.1, Q418.3
unnamed: Q417.1, Q419.3
unnamed: Q501.1, Q507.3
unnamed: Q502.1, Q508.3
unnamed: Q505.1, Q509.3
unnamed: Q506.1, Q510.3
unnamed: Q506.2, Q513.3, R503.2
unnamed: Q507.1, Q508.1, Q511.3
unnamed: Q508.2, Q514.3, Q515.3, Q516.2, R504.2
unnamed: Q509.1, Q510.1, Q512.3
unnamed: Q514.1, Q518.3
unnamed: Q517.1, Q519.3
unnamed: Q601.1, Q607.3
unnamed: Q602.1, Q608.3
unnamed: Q605.1, Q609.3
unnamed: Q606.1, Q610.3
unnamed: Q606.2, Q613.3, R603.2
unnamed: Q607.1, Q608.1, Q611.3
unnamed: Q608.2, Q614.3, Q615.3, Q616.2, R604.2
unnamed: Q609.1, Q610.1, Q612.3
unnamed: Q614.1, Q618.3
unnamed: Q617.1, Q619.3
unnamed: Q701.1, Q707.3
unnamed: Q702.1, Q708.3
unnamed: Q705.1, Q709.3
unnamed: Q706.1, Q710.3
unnamed: Q706.2, Q713.3, R703.2
unnamed: Q707.1, Q708.1, Q711.3
unnamed: Q708.2, Q714.3, Q715.3, Q716.2, R704.2
unnamed: Q709.1, Q710.1, Q712.3
unnamed: Q714.1, Q718.3
unnamed: Q717.1, Q719.3
unnamed: Q801.1, Q807.3
unnamed: Q802.1, Q808.3
unnamed: Q805.1, Q809.3
unnamed: Q806.1, Q810.3
unnamed: Q806.2, Q813.3, R803.2
unnamed: Q807.1, Q808.1, Q811.3
unnamed: Q808.2, Q814.3, Q815.3, Q816.2, R804.2
unnamed: Q809.1, Q810.1, Q812.3
unnamed: Q814.1, Q818.3
unnamed: Q817.1, Q819.3
unnamed: Q901.1, Q907.3
unnamed: Q902.1, Q908.3
unnamed: Q905.1, Q909.3
unnamed: Q906.1, Q910.3
unnamed: Q906.2, Q913.3, R903.2
unnamed: Q907.1, Q908.1, Q911.3
unnamed: Q908.2, Q914.3, Q915.3, Q916.2, R904.2
unnamed: Q909.1, Q910.1, Q912.3
unnamed: Q914.1, Q918.3
unnamed: Q917.1, Q919.3
unnamed: Q1001.1, Q1003.3
unnamed: Q1001.3, Q1002.2, R1001.2
unnamed: Q1101.1, Q1103.3
unnamed: Q1101.3, Q1102.2, R1101.2
unnamed: Q1201.1, Q1203.3
unnamed: Q1201.3, Q1202.2, R1201.2
unnamed: Q1301.1, Q1303.3
unnamed: Q1301.3, Q1302.2, R1301.2
unnamed: Q1401.1, Q1403.3
unnamed: Q1401.3, Q1402.2, R1401.2
unnamed: Q1501.1, Q1503.3
unnamed: Q1501.3, Q1502.2, R1501.2
unnamed: Q1601.1, Q1603.3
unnamed: Q1601.3, Q1602.2, R1601.2
VCC: J101.1, R101.1, R102.1, R103.1, R104.1, R201.1, R202.1, R203.1, R204.1, R205.1, R301.1, R302.1, R303.1, R304.1, R305.1, R401.1, R402.1, R403.1, R404.1, R405.1, R501.1, R502.1, R503.1, R504.1, R505.1, R601.1, R602.1, R603.1, R604.1, R605.1, R701.1, R702.1, R703.1, R704.1, R705.1, R801.1, R802.1, R803.1, R804.1, R805.1, R901.1, R902.1, R903.1, R904.1, R905.1, R1001.1, R1002.1, R1101.1, R1102.1, R1201.1, R1202.1, R1301.1, R1302.1, R1401.1, R1402.1, R1501.1, R1502.1, R1601.1, R1602.1

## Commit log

2017-12-31 DR1 added.
2018-01-05 Initial version of simulator.
2018-01-06 Implemented full simulator with I/O.
2018-01-07 Added assembler.
2018-01-07 Added sample programs and sample roms.
2018-01-17 Added kicad component libraries.
2018-01-17 Added clock design.
2018-01-17 Added register board design.
2019-08-27 Added licencing information.
2019-08-27 Changed around shift/rot opcodes.
2019-08-27 Added gitignore.
2019-08-27 Updated sample roms and asm samplies
2019-08-27 Updated register design to fix small flaw.
2019-08-27 Updated clock design.
2019-08-27 Updated component libraries to add components for memory and diode.
2019-08-27 Added adder design.
2019-08-27 Added design for program counter.
2019-08-27 Added mechanical eprom board design.
2019-08-27 Added logisim simulation of cpu.
2019-09-25 Added led component and footprint.
2019-09-25 Added test IO module.
2025-08-03 Latest design work updates.
